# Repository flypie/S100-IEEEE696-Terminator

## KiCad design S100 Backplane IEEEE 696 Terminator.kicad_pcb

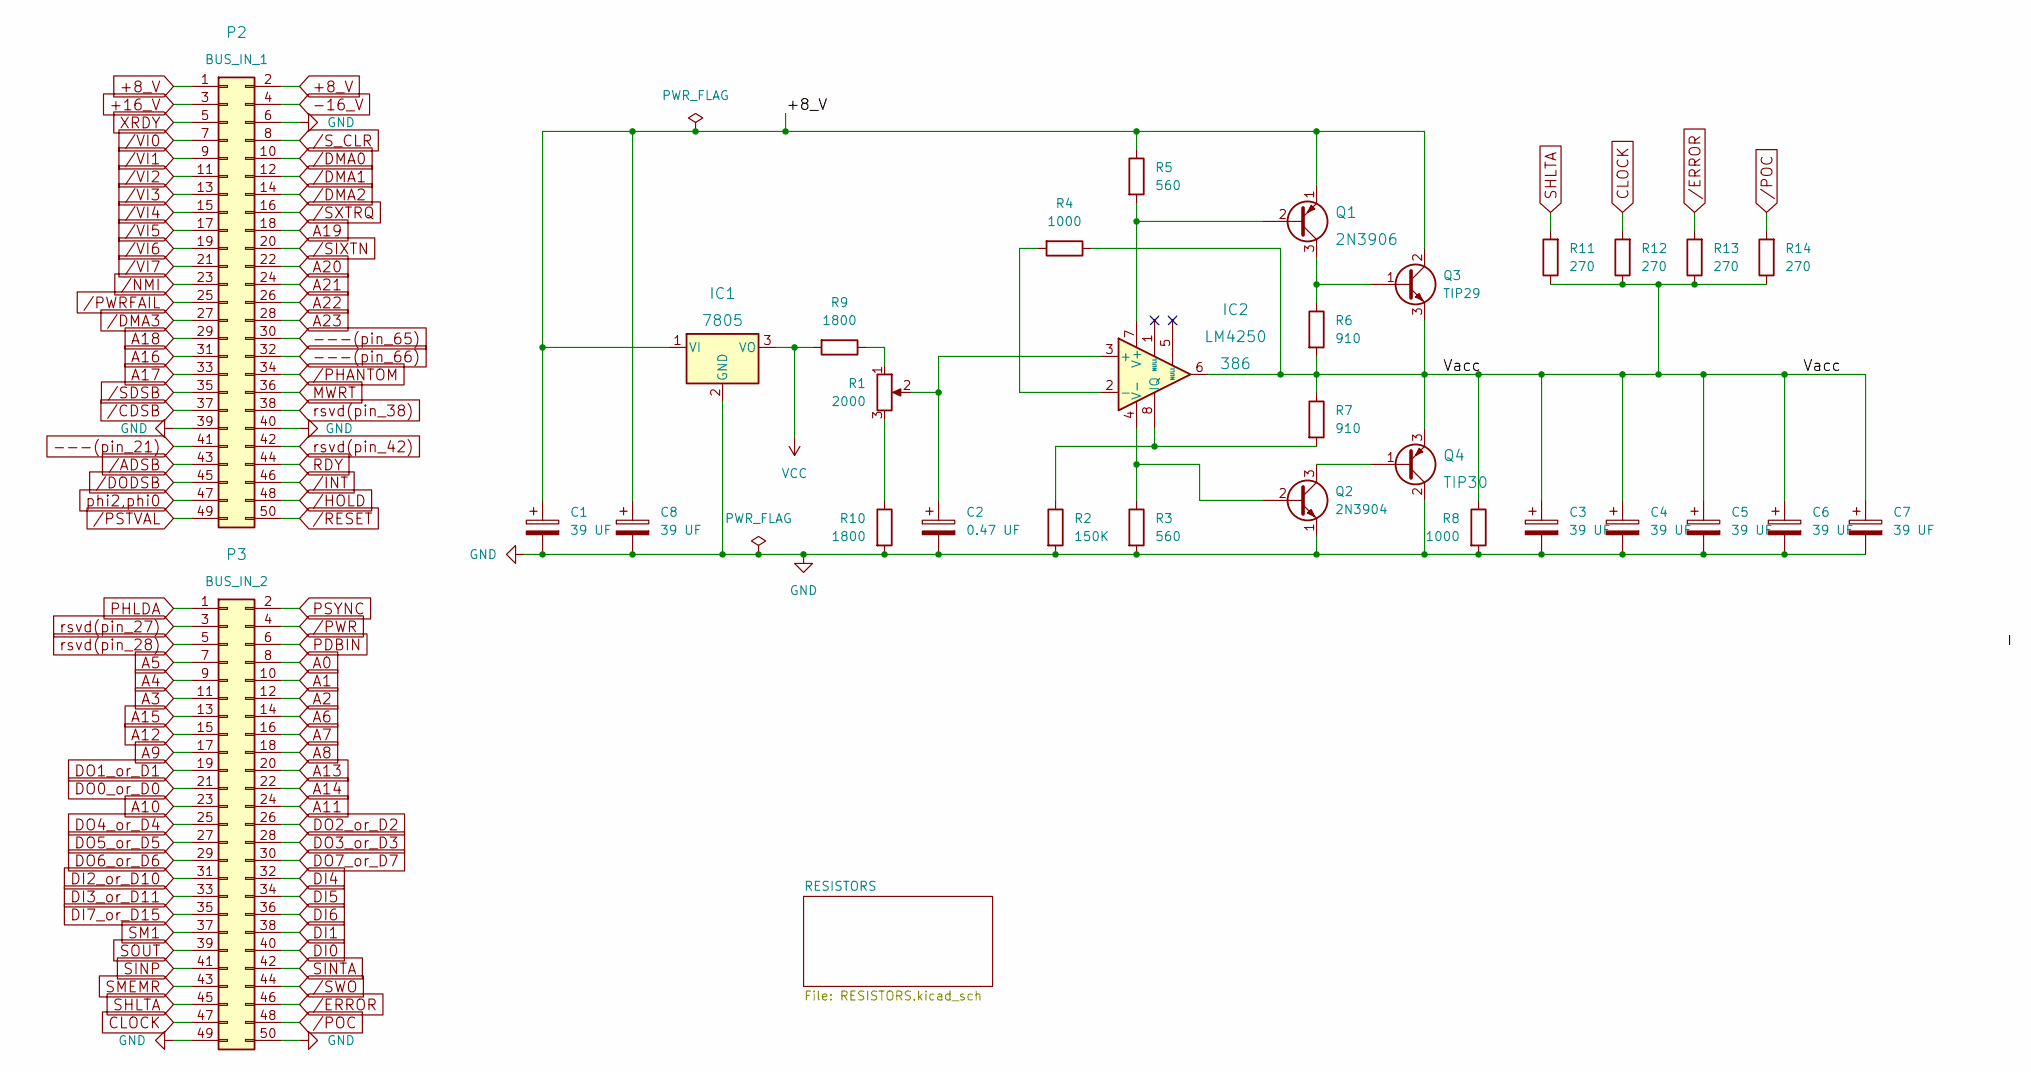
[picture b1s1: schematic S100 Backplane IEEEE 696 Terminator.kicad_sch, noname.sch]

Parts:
C1, C3: 39 UF; CP_Radial_D10.0mm_P5.00mm
C2: 0.47 UF; C_Axial_L5.1mm_D3.1mm_P10.00mm_Horizontal
C4, C5, C6, C7, C8: 39 UF; CP_Radial_Tantal_D6.0mm_P5.00mm
IC1: 7805; TO-220-3_Horizontal_TabDown
IC2: LM4250; DIP-8_W7.62mm
P2: BUS_IN_1; PinSocket_2x25_P2.54mm_Vertical
P3: BUS_IN_2; PinSocket_2x25_P2.54mm_Vertical
Q1: 2N3906; TO-92_Inline
Q2: 2N3904; TO-92_Inline
Q3: TIP29; TO-220-3_Horizontal_TabDown
Q4: TIP30; TO-220-3_Horizontal_TabDown
R1: 2000; Potentiometer_Vishay_T7-YA_Single_Vertical
R2: 150K; R_Axial_DIN0207_L6.3mm_D2.5mm_P10.16mm_Horizontal
R3, R5: 560; R_Axial_DIN0207_L6.3mm_D2.5mm_P10.16mm_Horizontal
R4, R8: 1000; R_Axial_DIN0207_L6.3mm_D2.5mm_P10.16mm_Horizontal
R6, R7: 910; R_Axial_DIN0207_L6.3mm_D2.5mm_P10.16mm_Horizontal
R9, R10: 1800; R_Axial_DIN0207_L6.3mm_D2.5mm_P10.16mm_Horizontal
R11, R12, R13, R14: 270; R_Axial_DIN0207_L6.3mm_D2.5mm_P2.54mm_Vertical

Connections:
+8_V: C1.1, C8.1, IC1.1 (VI), P2.1, P2.2, Q1.1 (E), Q3.2 (C), R5.1
+16_V: P2.3
-16_V: P2.4
---(pin_21): P2.41; also elsewhere on the board
---(pin_65): P2.30; also elsewhere on the board
---(pin_66): P2.32; also elsewhere on the board
/Vacc: C3.1, C4.1, C5.1, C6.1, C7.1, IC2.6, Q3.3 (E), Q4.3 (E), R4.1, R6.2, R7.1, R8.1, R11.1, R12.1, R13.1, R14.1
A0: P3.8; also elsewhere on the board
A1: P3.10; also elsewhere on the board
A2: P3.12; also elsewhere on the board
A3: P3.11; also elsewhere on the board
A4: P3.9; also elsewhere on the board
A5: P3.7; also elsewhere on the board
A6: P3.14; also elsewhere on the board
A7: P3.16; also elsewhere on the board
A8: P3.18; also elsewhere on the board
A9: P3.17; also elsewhere on the board
A10: P3.23; also elsewhere on the board
A11: P3.24; also elsewhere on the board
A12: P3.15; also elsewhere on the board
A13: P3.20; also elsewhere on the board
A14: P3.22; also elsewhere on the board
A15: P3.13; also elsewhere on the board
A16: P2.31; also elsewhere on the board
A17: P2.33; also elsewhere on the board
A18: P2.29; also elsewhere on the board
A19: P2.18; also elsewhere on the board
A20: P2.22; also elsewhere on the board
A21: P2.24; also elsewhere on the board
A22: P2.26; also elsewhere on the board
A23: P2.28; also elsewhere on the board
CLOCK: P3.47, R12.2
DI0: P3.40; also elsewhere on the board
DI1: P3.38; also elsewhere on the board
DI2_or_D10: P3.31; also elsewhere on the board
DI3_or_D11: P3.33; also elsewhere on the board
DI4: P3.32; also elsewhere on the board
DI5: P3.34; also elsewhere on the board
DI6: P3.36; also elsewhere on the board
DI7_or_D15: P3.35; also elsewhere on the board
DO0_or_D0: P3.21; also elsewhere on the board
DO1_or_D1: P3.19; also elsewhere on the board
DO2_or_D2: P3.26; also elsewhere on the board
DO3_or_D3: P3.28; also elsewhere on the board
DO4_or_D4: P3.25; also elsewhere on the board
DO5_or_D5: P3.27; also elsewhere on the board
DO6_or_D6: P3.29; also elsewhere on the board
DO7_or_D7: P3.30; also elsewhere on the board
GND: C1.2, C2.2, C3.2, C4.2, C5.2, C6.2, C7.2, C8.2, IC1.2 (GND), P2.6, P2.39, P2.40, P3.49, P3.50, Q2.1 (E), Q4.2 (C), R2.2, R3.2, R8.2, R10.2; also elsewhere on the board
MWRT: P2.36; also elsewhere on the board
unnamed: C2.1, IC2.3 (+), R1.2
unnamed: IC2.2 (-), R4.2
unnamed: IC2.4 (V-), Q2.2 (B), R3.1
unnamed: IC2.7 (V+), Q1.2 (B), R5.2
unnamed: IC2.8 (IQ), R2.1, R7.2
unnamed: Q1.3 (C), Q3.1 (B), R6.1
unnamed: Q2.3 (C), Q4.1 (B)
unnamed: R1.1, R9.1
unnamed: R1.3, R10.1
PDBIN: P3.6; also elsewhere on the board
PHLDA: P3.1; also elsewhere on the board
PSYNC: P3.2; also elsewhere on the board
RDY: P2.44; also elsewhere on the board
SHLTA: P3.45, R11.2
SINP: P3.41; also elsewhere on the board
SINTA: P3.42; also elsewhere on the board
SM1: P3.37; also elsewhere on the board
SMEMR: P3.43; also elsewhere on the board
SOUT: P3.39; also elsewhere on the board
VCC: IC1.3 (VO), R9.2
XRDY: P2.5; also elsewhere on the board
phi2,phi0: P2.47; also elsewhere on the board
rsvd(pin_27): P3.3; also elsewhere on the board
rsvd(pin_28): P3.5; also elsewhere on the board
rsvd(pin_38): P2.38; also elsewhere on the board
rsvd(pin_42): P2.42; also elsewhere on the board
/ADSB: P2.43; also elsewhere on the board
/CDSB: P2.37; also elsewhere on the board
/DMA0: P2.10; also elsewhere on the board
/DMA1: P2.12; also elsewhere on the board
/DMA2: P2.14; also elsewhere on the board
/DMA3: P2.27; also elsewhere on the board
/DODSB: P2.45; also elsewhere on the board
/HOLD: P2.48; also elsewhere on the board
/INT: P2.46; also elsewhere on the board
/NMI: P2.23; also elsewhere on the board
/POC: P3.48, R14.2
/PSTVAL: P2.49; also elsewhere on the board
/PWR: P3.4; also elsewhere on the board
/PWRFAIL: P2.25; also elsewhere on the board
/RESET: P2.50; also elsewhere on the board
/SDSB: P2.35; also elsewhere on the board
/SWO: P3.44; also elsewhere on the board
/SXTRQ: P2.16; also elsewhere on the board
/S_CLR: P2.8; also elsewhere on the board
/VI0: P2.7; also elsewhere on the board
/VI1: P2.9; also elsewhere on the board
/VI2: P2.11; also elsewhere on the board
/VI3: P2.13; also elsewhere on the board
/VI4: P2.15; also elsewhere on the board
/VI5: P2.17; also elsewhere on the board
/VI6: P2.19; also elsewhere on the board
/VI7: P2.21; also elsewhere on the board

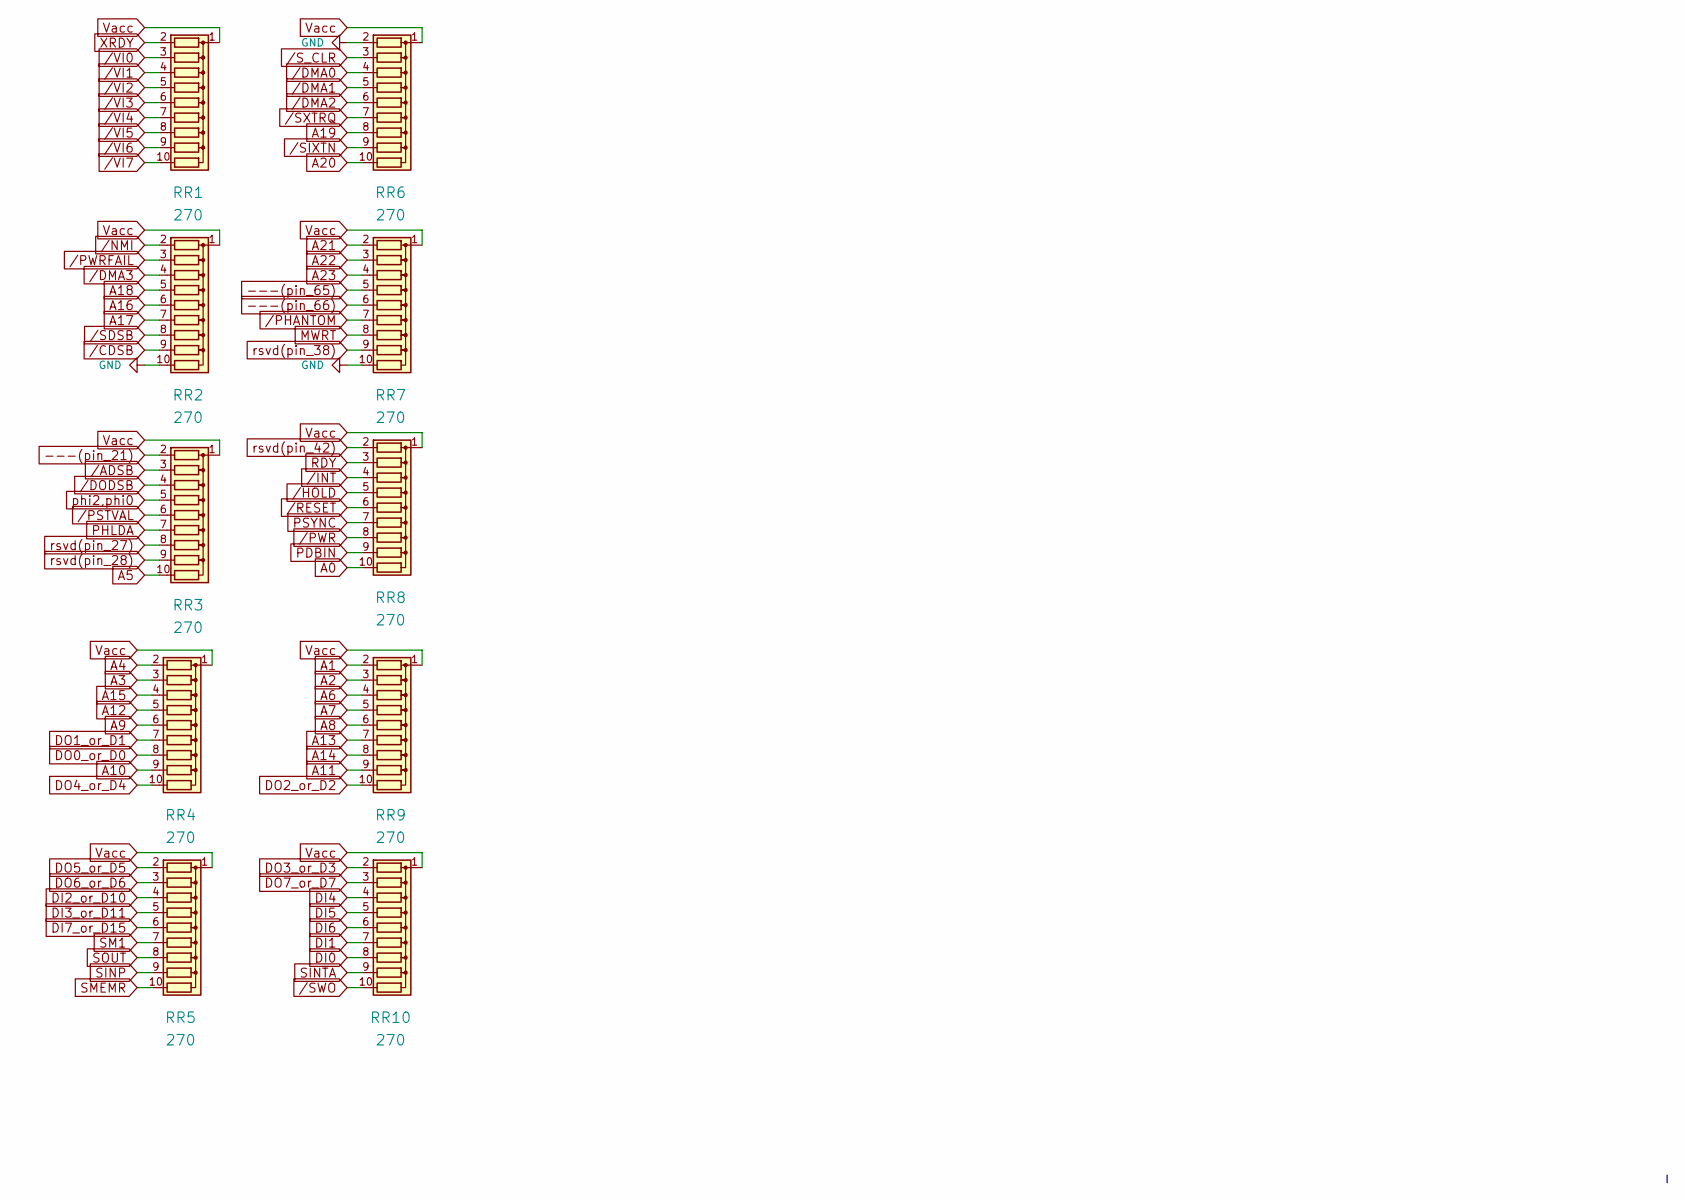
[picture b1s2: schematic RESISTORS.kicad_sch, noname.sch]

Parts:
RR1, RR2, RR3, RR4, RR5, RR6, RR7, RR8, RR9, RR10: 270; R_Array_SIP10

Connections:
---(pin_21): RR3.2 (R1); also elsewhere on the board
---(pin_65): RR7.5 (R4); also elsewhere on the board
---(pin_66): RR7.6 (R5); also elsewhere on the board
A0: RR8.10 (R9); also elsewhere on the board
A1: RR9.2 (R1); also elsewhere on the board
A2: RR9.3 (R2); also elsewhere on the board
A3: RR4.3 (R2); also elsewhere on the board
A4: RR4.2 (R1); also elsewhere on the board
A5: RR3.10 (R9); also elsewhere on the board
A6: RR9.4 (R3); also elsewhere on the board
A7: RR9.5 (R4); also elsewhere on the board
A8: RR9.6 (R5); also elsewhere on the board
A9: RR4.6 (R5); also elsewhere on the board
A10: RR4.9 (R8); also elsewhere on the board
A11: RR9.9 (R8); also elsewhere on the board
A12: RR4.5 (R4); also elsewhere on the board
A13: RR9.7 (R6); also elsewhere on the board
A14: RR9.8 (R7); also elsewhere on the board
A15: RR4.4 (R3); also elsewhere on the board
A16: RR2.6 (R5); also elsewhere on the board
A17: RR2.7 (R6); also elsewhere on the board
A18: RR2.5 (R4); also elsewhere on the board
A19: RR6.8 (R7); also elsewhere on the board
A20: RR6.10 (R9); also elsewhere on the board
A21: RR7.2 (R1); also elsewhere on the board
A22: RR7.3 (R2); also elsewhere on the board
A23: RR7.4 (R3); also elsewhere on the board
DI0: RR10.8 (R7); also elsewhere on the board
DI1: RR10.7 (R6); also elsewhere on the board
DI2_or_D10: RR5.4 (R3); also elsewhere on the board
DI3_or_D11: RR5.5 (R4); also elsewhere on the board
DI4: RR10.4 (R3); also elsewhere on the board
DI5: RR10.5 (R4); also elsewhere on the board
DI6: RR10.6 (R5); also elsewhere on the board
DI7_or_D15: RR5.6 (R5); also elsewhere on the board
DO0_or_D0: RR4.8 (R7); also elsewhere on the board
DO1_or_D1: RR4.7 (R6); also elsewhere on the board
DO2_or_D2: RR9.10 (R9); also elsewhere on the board
DO3_or_D3: RR10.2 (R1); also elsewhere on the board
DO4_or_D4: RR4.10 (R9); also elsewhere on the board
DO5_or_D5: RR5.2 (R1); also elsewhere on the board
DO6_or_D6: RR5.3 (R2); also elsewhere on the board
DO7_or_D7: RR10.3 (R2); also elsewhere on the board
GND: RR2.10 (R9), RR6.2 (R1), RR7.10 (R9); also elsewhere on the board
MWRT: RR7.8 (R7); also elsewhere on the board
PDBIN: RR8.9 (R8); also elsewhere on the board
PHLDA: RR3.7 (R6); also elsewhere on the board
PSYNC: RR8.7 (R6); also elsewhere on the board
RDY: RR8.3 (R2); also elsewhere on the board
SINP: RR5.9 (R8); also elsewhere on the board
SINTA: RR10.9 (R8); also elsewhere on the board
SM1: RR5.7 (R6); also elsewhere on the board
SMEMR: RR5.10 (R9); also elsewhere on the board
SOUT: RR5.8 (R7); also elsewhere on the board
Vacc: RR1.1 (common), RR2.1 (common), RR3.1 (common), RR4.1 (common), RR5.1 (common), RR6.1 (common), RR7.1 (common), RR8.1 (common), RR9.1 (common), RR10.1 (common)
XRDY: RR1.2 (R1); also elsewhere on the board
phi2,phi0: RR3.5 (R4); also elsewhere on the board
rsvd(pin_27): RR3.8 (R7); also elsewhere on the board
rsvd(pin_28): RR3.9 (R8); also elsewhere on the board
rsvd(pin_38): RR7.9 (R8); also elsewhere on the board
rsvd(pin_42): RR8.2 (R1); also elsewhere on the board
/ADSB: RR3.3 (R2); also elsewhere on the board
/CDSB: RR2.9 (R8); also elsewhere on the board
/DMA0: RR6.4 (R3); also elsewhere on the board
/DMA1: RR6.5 (R4); also elsewhere on the board
/DMA2: RR6.6 (R5); also elsewhere on the board
/DMA3: RR2.4 (R3); also elsewhere on the board
/DODSB: RR3.4 (R3); also elsewhere on the board
/HOLD: RR8.5 (R4); also elsewhere on the board
/INT: RR8.4 (R3); also elsewhere on the board
/NMI: RR2.2 (R1); also elsewhere on the board
/PSTVAL: RR3.6 (R5); also elsewhere on the board
/PWR: RR8.8 (R7); also elsewhere on the board
/PWRFAIL: RR2.3 (R2); also elsewhere on the board
/RESET: RR8.6 (R5); also elsewhere on the board
/SDSB: RR2.8 (R7); also elsewhere on the board
/SWO: RR10.10 (R9); also elsewhere on the board
/SXTRQ: RR6.7 (R6); also elsewhere on the board
/S_CLR: RR6.3 (R2); also elsewhere on the board
/VI0: RR1.3 (R2); also elsewhere on the board
/VI1: RR1.4 (R3); also elsewhere on the board
/VI2: RR1.5 (R4); also elsewhere on the board
/VI3: RR1.6 (R5); also elsewhere on the board
/VI4: RR1.7 (R6); also elsewhere on the board
/VI5: RR1.8 (R7); also elsewhere on the board
/VI6: RR1.9 (R8); also elsewhere on the board
/VI7: RR1.10 (R9); also elsewhere on the board

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
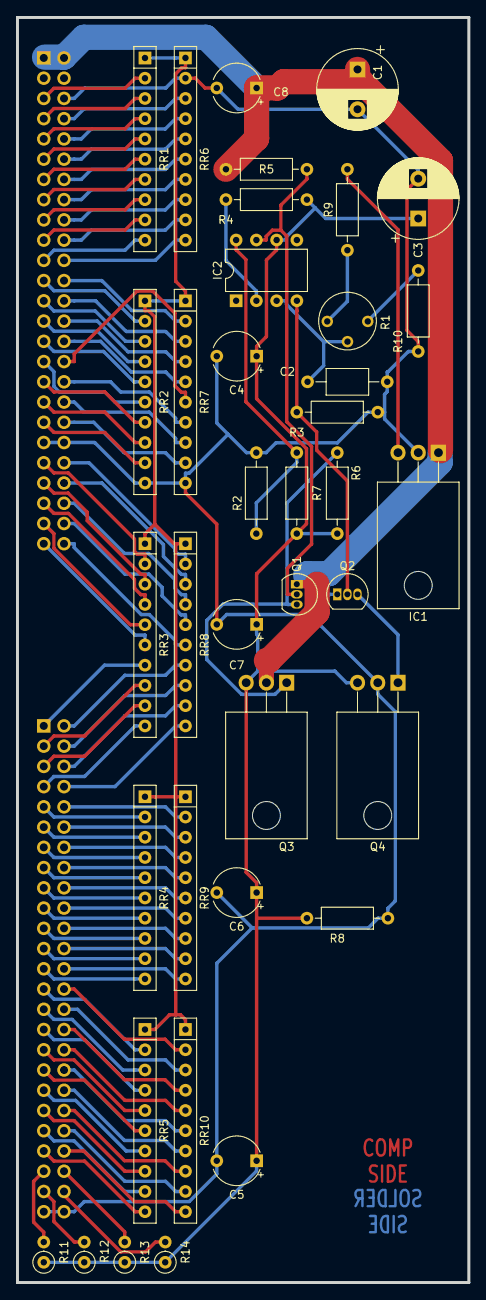
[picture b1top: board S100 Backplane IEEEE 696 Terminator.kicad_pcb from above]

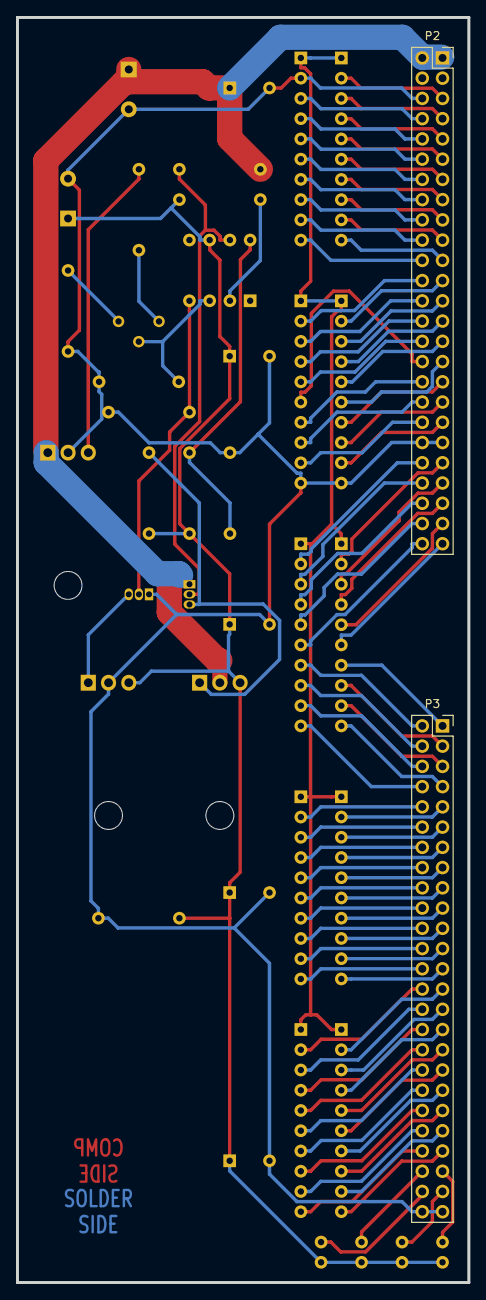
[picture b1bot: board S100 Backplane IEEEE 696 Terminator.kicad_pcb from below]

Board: 2 copper layers, 56.6 x 158.8 mm, 40 parts (2 on the bottom side), 105 nets.

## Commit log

2022-03-28 First stab at this.
2022-03-28 Fix minor problem.
